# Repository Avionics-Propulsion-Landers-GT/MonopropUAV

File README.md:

# MonopropUAV
Project files + resources for the Monoprop UAV project

**Google Drives:**
Please check these Drive folders for meeting slides, resources, etc.

[Algorithms](https://drive.google.com/drive/folders/1vxY-udHqTgmarN2Y4lALjIYDhyv2OA7N?usp=sharing)

[Electronics](https://drive.google.com/drive/folders/1lZPJO9E9syAnoeq-bsbVtlA1xF-AGdLT?usp=sharing)

[Sensing & Control](https://drive.google.com/drive/folders/1B5el5EHVFndY2es_LnUI2bg67gWon6B9?usp=sharing)

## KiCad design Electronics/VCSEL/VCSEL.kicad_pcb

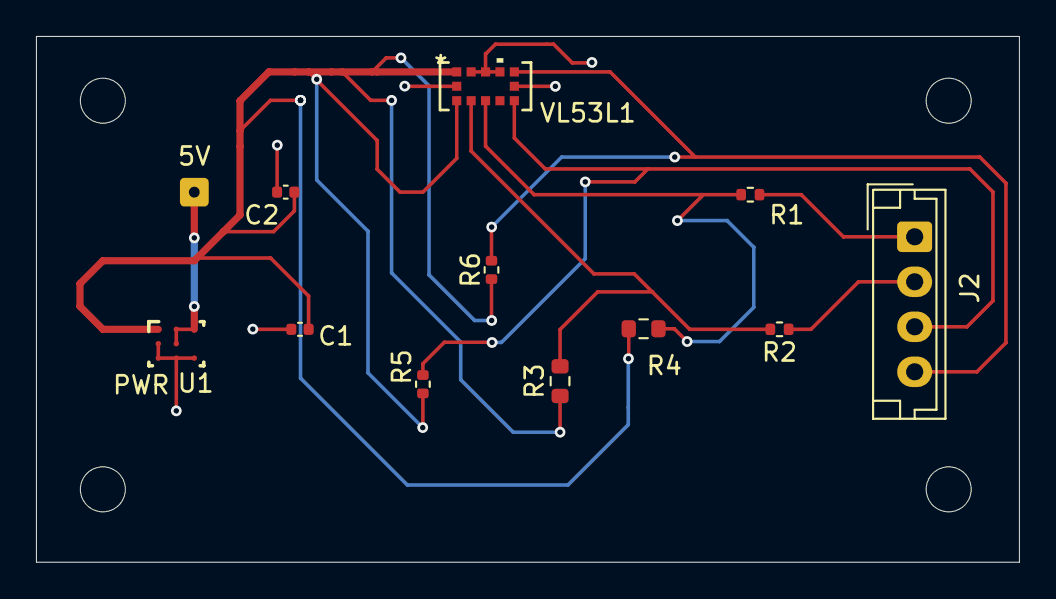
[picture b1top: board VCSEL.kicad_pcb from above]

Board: 2 copper layers, 54.6 x 29.2 mm, 12 parts (0 on the bottom side), 9 nets.

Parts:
5V: 5V; SolderWire-0.1sqmm_1x01_D0.4mm_OD1mm
C1: 100 nF; C_0402_1005Metric
C2: 4.7 μF; C_0402_1005Metric
J2: Conn_01x04; JST_EH_B4B-EH-A_1x04_P2.50mm_Vertical
R1, R2: 100Ω; R_0402_1005Metric
R3, R4: R_0603_1608Metric
R5, R6: 10kΩ; R_0402_1005Metric
U1: TPS82698SIPR; SIP0008A
VL53L1: QFN_BV0FY&slash_1_STM

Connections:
+5V: 5V.1, U1.A2 (VIN), U1.A3 (VIN), U1.B2 (EN)
/GPIO1: J2.3, R5.2, VL53L1.7 (GPIO1)
/I2C SCL: R2.1, R3.2, VL53L1.10 (SCL)
/I2C SDA: R1.1, R4.2, VL53L1.9 (SDA)
GND: C1.2, C2.2, U1.B1 (MODE), U1.C1 (GND), U1.C2 (GND), U1.C3 (GND), VL53L1.2 (AVSSVCSEL), VL53L1.3 (GND), VL53L1.4 (GND2), VL53L1.6 (GND3), VL53L1.12 (GND4)
unnamed: C1.1, C2.1, R3.1, R4.1, R5.1, R6.1, U1.A1 (VOUT), VL53L1.1 (AVDDVCSEL), VL53L1.11 (AVDD)
SCLout: J2.2, R2.2
SDAout: J2.1, R1.2
XSHUT: J2.4, R6.2, VL53L1.5 (XSHUT)

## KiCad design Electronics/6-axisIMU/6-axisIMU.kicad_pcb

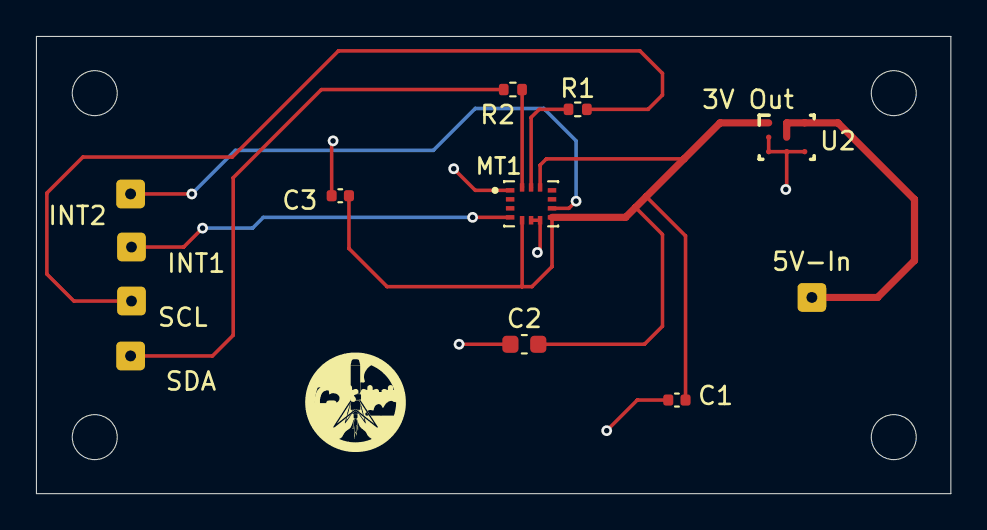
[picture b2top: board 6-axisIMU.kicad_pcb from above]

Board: 2 copper layers, 50.8 x 25.4 mm, 12 parts (0 on the bottom side), 8 nets.

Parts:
5V-In: SolderWire-0.1sqmm_1x01_D0.4mm_OD1mm
C1: 0.1µF; C_0402_1005Metric
C2: 2.2µF; C_0603_1608Metric
C3: 10 nF; C_0402_1005Metric
INT1, INT2: SolderWire-0.1sqmm_1x01_D0.4mm_OD1mm
MT1: ICM-42670-P; XDCR_ICM-42670-P
R1, R2: 10kΩ; R_0402_1005Metric
SCL: SolderWire-0.1sqmm_1x01_D0.4mm_OD1mm
SDA: SolderWire-0.1sqmm_1x01_D0.4mm_OD1mm
U2: TPS82698SIPR; SIP0008A

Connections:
+5V: 5V-In.1, U2.A2 (VIN), U2.A3 (VIN), U2.B2 (EN)
/INT1: INT1.1, MT1.4 (INT1/INT)
/INT2: INT2.1, MT1.9 (INT2)
GND: C1.1, C2.1, C3.2, MT1.1 (AP_SDO/AP_AD0), MT1.6 (GND), MT1.7 (FSYNC), U2.B1 (MODE), U2.C1 (GND), U2.C2 (GND), U2.C3 (GND)
unnamed: C1.2, C2.2, C3.1, MT1.5 (VDDIO), MT1.8 (VDD), MT1.12 (AP_CS), U2.A1 (VOUT)
unnamed: MT1.13 (AP_SCL/AP_SCLK), R1.1
unnamed: MT1.14 (AP_SDA/AP_SDIO/AP_SDI), R2.1
SCL: R1.2, SCL.1

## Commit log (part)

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2025-04-11 Added K and calculation of U via LQR
2025-04-12 add symbolic only func for LQR A/B + adjust num lqr to only perform num operations
2025-04-13 Add first stage integrated dyn model + adjust matrix / vector classes in custom linear alongside quaternion
2025-04-13 add plotter to show the position of the monoprop vs iteration step (wip)
2025-04-13 fix cpp dyn model, add cmake file & adjust integratedplotter (does not work)
2025-04-14 remove build files, adjust integrated model mass, record command history, set negative K to zero, simplify traj for debug
2025-04-15 Added bash script and gitignore for build
2025-04-15 Pushing *somewhat* working LQR
2025-04-17 integrated imu
2025-04-18 50m hop
2025-04-18 create LQR in BF matlab
2025-04-22 update cdRegression in dynamics model
2025-04-22 correct units related to Cd calculation
2025-04-29 renamed stuff + started purge of unsused variables
2025-04-30 add simulated gaussian noise + random-walk bias to sensor measurement
2025-04-30 add lat/lon measurements + helper funcs to mock gps data
2025-05-01 add attitude (physical) plot for debugging
2025-05-01 fix cd reg in dynmodel
2025-05-02 added debiasing
2025-05-03 pushing changes
2025-05-04 added aero
2025-05-04 started firmware
2025-05-04 added more pio stuff
2025-05-04 dt made
2025-05-04 dt fix
2025-05-04 pull again nathan
2025-05-04 no more delay
2025-05-04 pio run success
2025-05-04 snipping bits of loop firmware
2025-05-04 coordinating
2025-05-04 pushin
2025-05-05 Create Direct Access Setup + HTML
2025-05-05 Add files via upload
    Datasheet for the ESP32 WROOM
2025-05-05 almost done with command to avionics
2025-05-06 setting up teensy
2025-05-06 build successful
2025-05-12 add plotter (copied from control loop folder) + add missing plots
2025-05-12 created initial mpc controller. does not work rn
2025-05-12 debugging (runs now)
2025-05-13 aligned values between DM and MPC.
2025-05-13 add simplified mpc for learning/debugging
2025-05-14 update simplified mpc to current standards (todo: deprecate old mpc ipynb)
2025-05-14 ang accel fixed
2025-05-14 deleted deprecated files
2025-05-15 merging
2025-05-15 minimum mass constraint
2025-05-16 add C_d regression
2025-05-17 changed dynamics model to use euler angles exclusively (still not working)
2025-05-17 integrated MPC with inhouse dynamics model (working)
2025-05-18 adjusted cost matrices
2025-05-20 fix bad torque calc in state space model, add stronger wind during ascent, adjust tunings.
2025-05-21 corrected x->longitude and y-> latitude
2025-05-21 final tweak to long lat conversions
2025-06-11 setting up lossless solving, gotta review the papers a bit more
2025-06-27 Create Read Me
    All the files for the design of signal conditioning board process will be uploaded here.
2025-06-30 Created 1D Rocket Fuel Sim for preliminary fuel estimates
2025-07-20 Created simulation for IMU at rest
2025-07-24 Added lidar at rest simulation data
2025-07-24 moving to main
2025-08-18 minor changes to lossless and added simulation results from dynamics model
2025-08-19 working on refining thrust constraints
2025-08-25 lossless does work backwards if the glide slope constraint is removed
2025-09-04 Update nonlinear MPC for TVC rocket dynamics
    Refactor nonlinear MPC for generic TVC rocket dynamics. Still does not account for the actual dynamics of the monoprop.
    TO DO: Update model dynamics to reflect changing COM.
2025-09-06 Add NMPC crate for nonlinear model predictive control in Rust
    Implement Nonlinear Model Predictive Control (NMPC) crate with dynamics, Jacobian computation, trajectory rollout, and QP solver functions. This crate is meant to be used by a main.rs file.
2025-09-06 Document usage of Rust NMPC implementation
    Added instructions for using the Rust implementation of NMPC, including installation, dependencies, build, run, and result checking.
2025-09-06 Upload example output graphs from Rust MPC
2025-10-01 9 axis Imu Code - Jackson R
    This is my first version, has not been tested. Initializes and defines sensor, reads data, and stores in a csv.file on an Sd card on the teensy.
2025-10-06 VL53L1X Distance Sensor
    initializing and operating VL53L1X distance sensor using I2C
2025-10-24 starting on work with the rust version of lossless
2025-10-25 fix madgwick filter euler angle calculations
    Actually made the formulas match the source website 😭
2025-10-27 Integrate OpEn solver for MPC optimization
    Added the optimization_engine crate and implemented an OpEn solver for the MPC problem, replacing the previous SQP/PGD approach in main.rs. Updated reference setpoints, cost weights, and plotting col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
    Issues:
    OpEn is slower, most likely due to calculation of Jacobian for the cost gradient. Will need to look into matrix derivatives of the quadratic program for the gradient.
2025-11-10 very rough hashing out of lossless rust solver
2025-11-18 Tune MPC parameters and add control smoothing
    Updated reference setpoints, cost weights, and control input bounds in main.rs for a more realistic rocket model. Increased rocket mass and inertia in mpc_crate.rs, and added control input smoothing 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
2025-11-24 Add EKF implementation library and models in rust
    Implemented an EKF struct and EKFModel Trait as well as implementations of the EKFModel trait for GPS, LiDAR, and IMU sensors.
2025-12-10 continued work on conventional lossless rust algorithm. first two socp constraints converge individually but not together
2025-12-13 Successfully added glide slope constraint and coarse/fine solving capability like the python version has. Essentially, rust conventional lossless is done.
2025-12-23 Add Chebyshev Lossless Baseplate
    Created a new file referncing our discrete lossless implementation with guidelines for how to implement a parameterized Lossless implementation using Chebyshev polynmoials
2025-12-28 maybe this time it will be fixed
2026-01-09 dummy funcs for extracting chebyshev results
2026-01-19 Add realistic dynamics function for lander
2026-01-19 Add NMPC crate with dynamics and QP solver
    Implement Nonlinear Model Predictive Control (NMPC) crate with dynamics, Jacobian computation, trajectory rollout, and QP solver functionalities.
2026-01-19 Add control smoothing
    Add better control smoothing to MPC algorithm, done using an exponential filter.
    Issue: setting an initial reference point close to the origin when the rocket is on the ground causes MPC algorithm to calculate close to minimum thrust. Smaller thrust causes gimbal angles to go cra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
2026-01-19 Create README.md for control loop
2026-01-19 further work on the rocket simulation, added in all key subsystems
2026-01-20 Fix Build Bugs with Rust-EKF and Created Library Modules to access MPC and Lossless structs and implementations
2026-01-26 add CGL nodes, setup D matrix
2026-01-29 Started work on chebyshev constraints, mostly just added some gpt framework and a clenshaw-curtis weights function
2026-02-03 Add MPC module and sequence-based commands
    Integrate mpc within the control loop. Clarify quaternion ordering and replace single thrust/target attitude with control sequence fields (thrust_seq, gimbal_theta_seq, gimbal_phi_seq) in GroundComma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
2026-02-04 Add user input commands and landing logic
    Introduce ground-control commands such as go, land, and kill.
    Add landing procedure and landing thrust scaling: when landing is initiated and altitude is near ground, scale thrust linearly to zero over 2s and then deactivate control.
2026-02-07 Invert sum_coeff, add comments
2026-02-08 Remove completed TODO
2026-02-10 checked all chebyshev inequality constraints, with some small removal of TODOs and inefficiency in the standard rust lossless file. next, we need to be able to parse the trajectory
2026-02-14 barycentric weights and scalar evaluation
2026-02-14 added note for extract result
2026-02-14 fix sigma_idx for clenshaw weights
2026-02-15 Fixes lower thrust bound issues on chebyshev and standard lossless
2026-02-17 Creates test program with rerun viewer for basic physics
2026-02-18 Adds in center of mass vectors to the tanks and tvc module
2026-02-18 adds functions to get mass and state
2026-02-19 Adds min thrust, max thrust, and gimbal limit variables to MPC constraints
2026-02-20 Adjusts weights for MPC in simulation and adds mass input
2026-02-23 Adds ZOH ground truth for 50m unbounded descent
2026-02-24 Adds ZOH offset ground truth path
2026-02-24 Adds a 5 m/s velocity limited ground truth
2026-02-24 Revert "rsme normalized"
    This reverts commit 027d9039f186e85ebc58dad61d8ea1ba6428f93f.
2026-02-24 sensor fusion
2026-02-25 converges!
2026-02-25 yay data
2026-02-25 add med run for direct descent
2026-02-25 offset run
2026-02-25 Adds 5 vel limit offset truth
2026-02-26 add more to direct_limited (even tho its really offset_limited)
2026-02-26 ultra short & extreme long :D
2026-02-26 add more to direct descent, start direct_limited
2026-02-26 graph short direct descent difference
2026-02-26 ahhhh it all makes sense now
2026-02-26 aghhhh part 2
2026-02-26 ok this might work :pray
2026-02-26 that's gotta be good enough :sob
2026-02-26 add direct limited short
2026-02-26 add very short
2026-02-26 ultra_short
2026-02-26 finish adding offset_limited_descent
2026-02-26 ultra_short direct_descent
2026-02-26 add direct short
2026-02-26 graphs!
2026-02-26 more human readable
2026-02-26 offset short
2026-02-26 add uxyz
2026-02-26 add extreme_short for offset_descent
2026-02-26 make data good :)
2026-02-26 first attempt extreme short descent limited
2026-02-26 cleanup
2026-02-26 Fix OpEn solver function
    Add a new OpEnSolve implementation in mpc_crate.rs that formulates/solves the delta-U QP with PANOC (shifted bounds, smoothing cost, clamping) and returns the applied input and full sequence. Old OpE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
2026-02-27 more trajs
2026-02-27 final graphs (it's finally over)
2026-03-01 Add wind sim module with altitude profile and Gauss-Markov gust model
2026-03-01 Add get_wind_model helper and wire wind model into get_rocket
2026-03-01 Switch Rerun to buffered mode so sim and CSV always run without the viewer
2026-03-02 Adds one more tuning for final landing
2026-03-04 Adds MOI customization, still needs full inertia
2026-03-05 Adds simulation.rs, which packages the previous main.rs into a struct. Also adds linear actuator specs
2026-03-07 Moves main sim loop to simulation.rs and adds imu data
2026-03-08 draft for the 9-axis IMU EKF in rust
2026-03-11 adding tester based on a csv of the 9-axis IMU data + simulation viewer in python to see the output
2026-03-12 update average solve time graph
2026-03-12 Refactors fluid_dynamics.rs to fit in structs, and adds default() functions to simulation components for easier readability
2026-03-14 feat(aero): define AeroRecord struct with serde Deserialize
2026-03-14 feat(aero): add bilinear_interp helper for 2-D table interpolation
2026-03-14 test(aero): add hermetic unit tests for lookup, clamping, bilinear midpoint
2026-03-14 feat(physics): replace static drag with ISA-density table lookup and fallback
2026-03-16 feat(main): wire AeroTable into get_rocket and log aero metrics
2026-03-17 bash script to test attitude
2026-03-17 final draft for the 9-axis IMU EKF in rust, kinda tweaks at the beginning
2026-03-18 Adjusts implementation of aero to better fit with current simulation scheme
2026-03-18 6-axis IMU built off the 9-axis model
2026-03-22 feat(aero): update lookup table for lander 180deg alpha / mach 0.05 regime
2026-03-31 mtv sim and folder
2026-03-31 MTV sim in folder + gitignored logs
2026-04-02 chore(aero): remove visualize_csv.py tool for now
2026-04-02 Working on implementing better algorithm refresh
2026-04-06 Remove Tokio and Async
    This is mostly used for I/O operations or networking not the best choice for Realtime Hardware Operations
2026-04-07 Add TODO tasks for termination/failure procedures
2026-04-14 beautiful graphs :)
2026-04-14 Add Valve on/off struct to device_sim
2026-04-14 Wire o-iso, r-mv, o-vnt valves into fluid dynamics solver
2026-04-15 moreee cleanup
2026-04-15 hard tube :0
2026-04-15 feat(sim): add line_vol_r_mv parameter to ThermoFluidParameters
2026-04-15 feat(sim): add pressure tap-point fields to FluidDynamicsOutput
2026-04-15 feat(sim): add PT fields to Rocket struct, constructor, and default
